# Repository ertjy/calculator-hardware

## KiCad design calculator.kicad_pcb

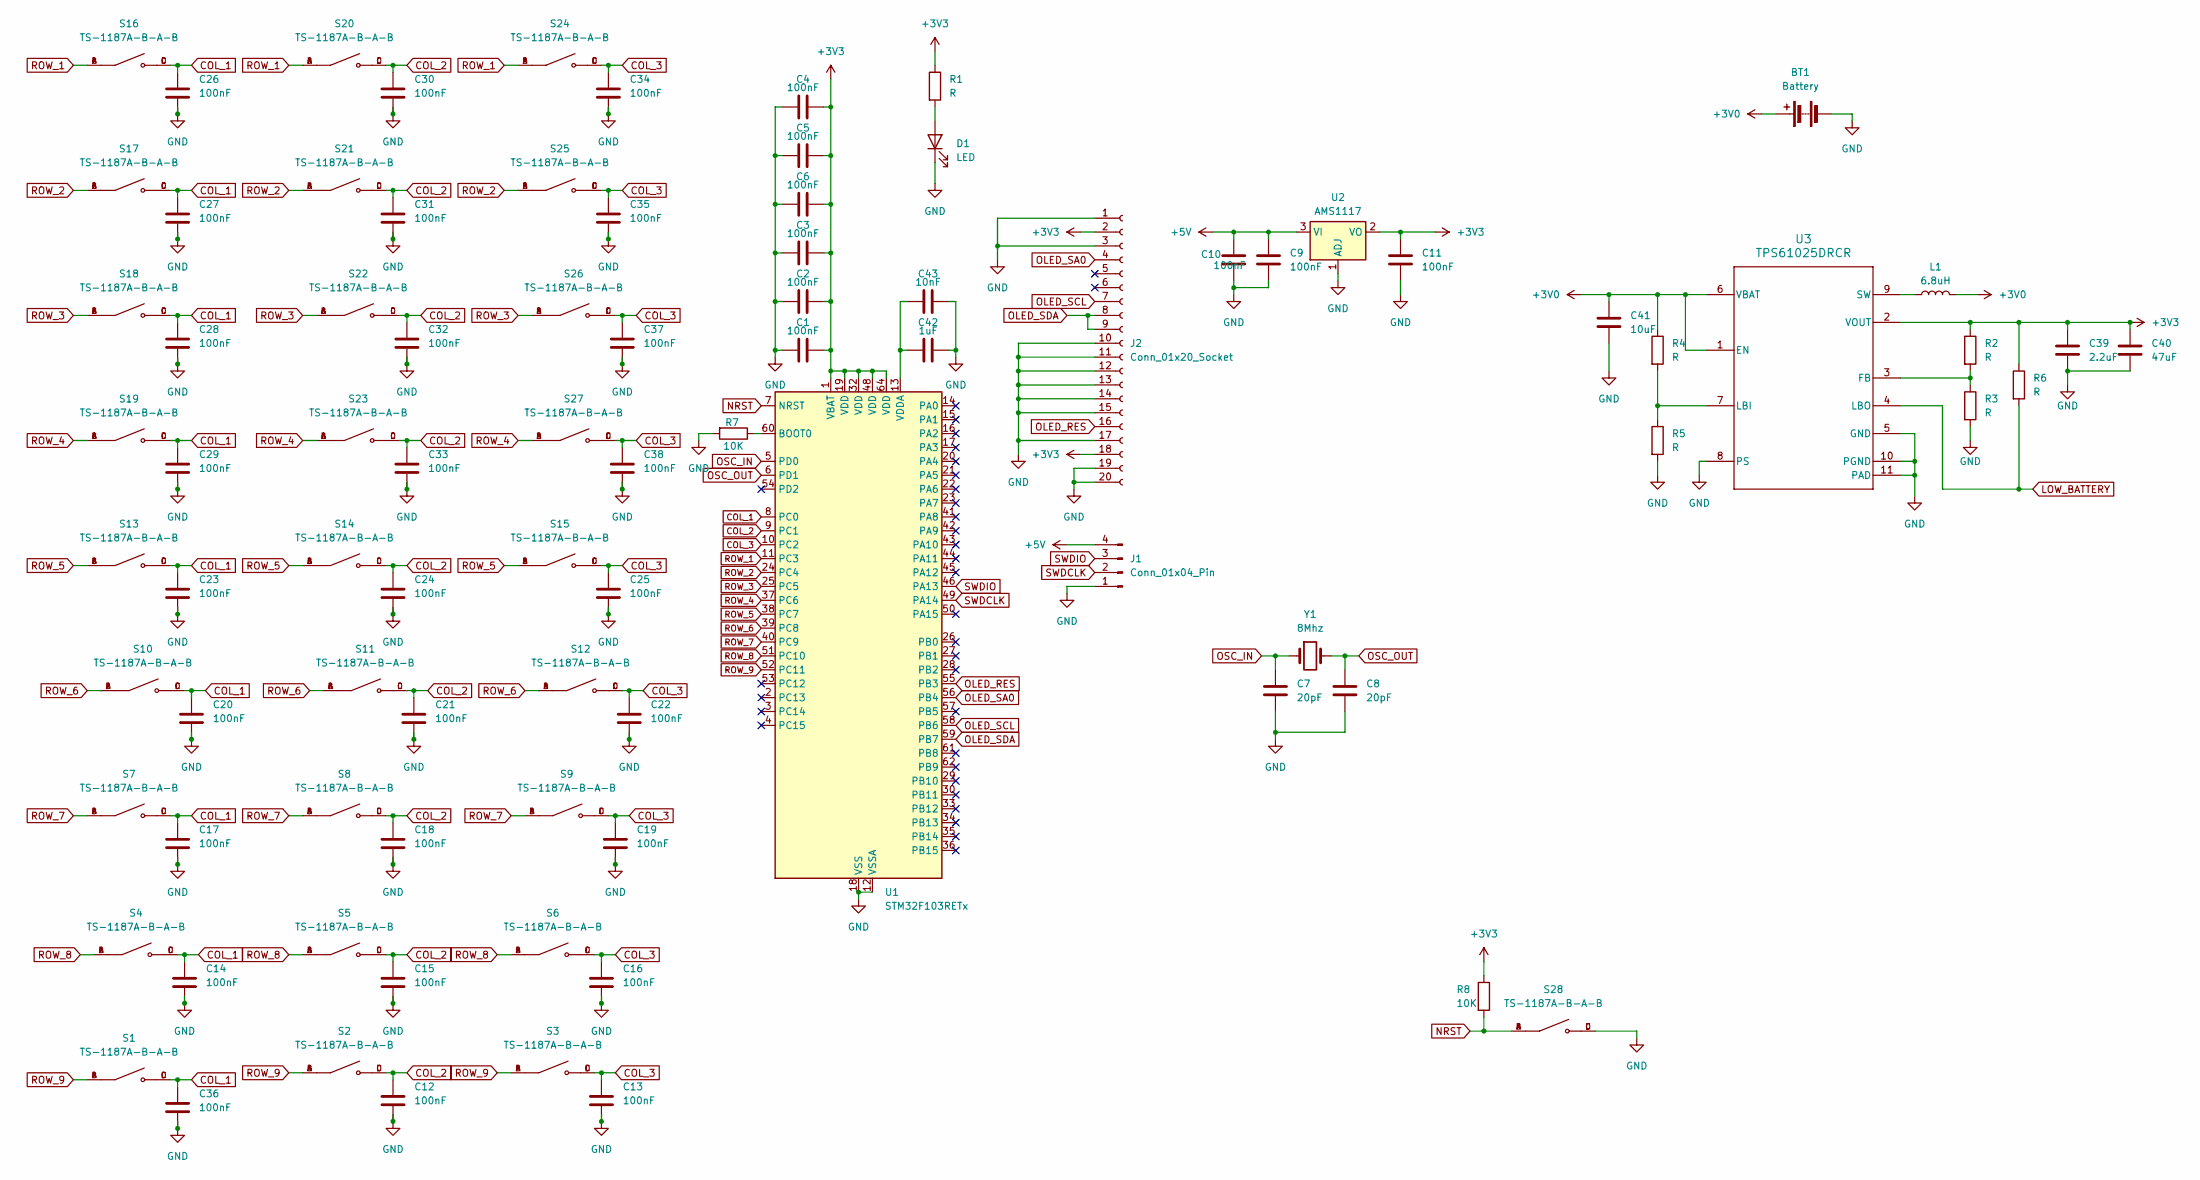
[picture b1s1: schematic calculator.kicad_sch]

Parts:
BT1: Battery; Battery_Pads
C1, C2, C3, C4, C5, C6, C9, C10, C11, C12, C13, C14, C15, C16, C17, C18, C19, C20, C21, C22, C23, C24, C25, C26, C27, C28, C29, C30, C31, C32, C33, C34, C35, C36, C37, C38: 100nF; C_0603_1608Metric
C7, C8: 20pF; C_0603_1608Metric
C39: 2.2uF; C_0603_1608Metric
C40: 47uF; C_0805_2012Metric
C41: 10uF; C_0603_1608Metric
C42: 1uF; C_0603_1608Metric
C43: 10nF; C_0603_1608Metric
D1: LED; LED_0603_1608Metric
J1: Conn_01x04_Pin; PinHeader_1x04_P2.54mm_Vertical
J2: Conn_01x20_Socket; PinSocket_1x20_P2.54mm_Vertical
L1: 6.8uH; IND_NP-4R7NC_SUM
R1, R2, R3, R4, R5, R6: R; R_0201_0603Metric
R7, R8: 10K; R_0201_0603Metric
S1, S2, S3, S4, S5, S6, S7, S8, S9, S10, S11, S12, S13, S14, S15, S16, S17, S18, S19, S20, S21, S22, S23, S24, S25, S26, S27, S28: TS-1187A-B-A-B; SW_TS-1187A-B-A-B; PARTREV A0
U1: STM32F103RETx; LQFP-64_10x10mm_P0.5mm
U2: AMS1117; SOT-223-3_TabPin2
U3: TPS61025DRCR; DRC0010J
Y1: 8Mhz; Crystal_SMD_HC49-SD

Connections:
+3V0: BT1.1 (+), C41.1, L1.2, R4.1, U3.1 (EN), U3.6 (VBAT)
+3V3: C1.2, C2.2, C3.2, C4.2, C5.2, C6.2, C11.1, C39.1, C40.1, J2.2, J2.18, R1.1, R2.1, R6.1, R8.1, U1.1 (VBAT), U1.19 (VDD), U1.32 (VDD), U1.48 (VDD), U1.64 (VDD), U2.2 (VO), U3.2 (VOUT)
+5V: C9.1, C10.2, J1.4, U2.3 (VI)
COL_1: C14.1, C17.1, C20.1, C23.1, C26.1, C27.1, C28.1, C29.1, C36.1, S1.C, S1.D, S4.C, S4.D, S7.C, S7.D, S10.C, S10.D, S13.C, S13.D, S16.C, S16.D, S17.C, S17.D, S18.C, S18.D, S19.C, S19.D, U1.8 (PC0)
COL_2: C12.1, C15.1, C18.1, C21.1, C24.1, C30.1, C31.1, C32.1, C33.1, S2.C, S2.D, S5.C, S5.D, S8.C, S8.D, S11.C, S11.D, S14.C, S14.D, S20.C, S20.D, S21.C, S21.D, S22.C, S22.D, S23.C, S23.D, U1.9 (PC1)
COL_3: C13.1, C16.1, C19.1, C22.1, C25.1, C34.1, C35.1, C37.1, C38.1, S3.C, S3.D, S6.C, S6.D, S9.C, S9.D, S12.C, S12.D, S15.C, S15.D, S24.C, S24.D, S25.C, S25.D, S26.C, S26.D, S27.C, S27.D, U1.10 (PC2)
GND: BT1.2 (-), C1.1, C2.1, C3.1, C4.1, C5.1, C6.1, C7.1, C8.1, C9.2, C10.1, C11.2, C12.2, C13.2, C14.2, C15.2, C16.2, C17.2, C18.2, C19.2, C20.2, C21.2, C22.2, C23.2, C24.2, C25.2, C26.2, C27.2, C28.2, C29.2, C30.2, C31.2, C32.2, C33.2, C34.2, C35.2, C36.2, C37.2, C38.2, C39.2, C40.2, C41.2, C42.2, C43.2, D1.1 (K), J1.1, J2.1, J2.3, J2.10, J2.11, J2.12, J2.13, J2.14, J2.15, J2.17, J2.19, J2.20, R3.2, R5.2, R7.2, S28.C, S28.D, U1.12 (VSSA), U1.18 (VSS), U1.31 (VSS), U1.47 (VSS), U1.63 (VSS), U2.1 (ADJ), U3.5 (GND), U3.8 (PS), U3.10 (PGND), U3.11 (PAD)
LOW_BATTERY: R6.2, U3.4 (LBO)
NRST: R8.2, S28.A, S28.B, U1.7 (NRST)
unnamed: D1.2 (A), R1.2
unnamed: R7.1, U1.60 (BOOT0)
unnamed: C42.1, C43.1, U1.13 (VDDA)
unnamed: R2.2, R3.1, U3.3 (FB)
unnamed: R4.2, R5.1, U3.7 (LBI)
unnamed: L1.1, U3.9 (SW)
OLED_RES: J2.16, U1.55 (PB3)
OLED_SA0: J2.4, U1.56 (PB4)
OLED_SCL: J2.7, U1.58 (PB6)
OLED_SDA: J2.8, J2.9, U1.59 (PB7)
OSC_IN: C7.2, U1.5 (PD0), Y1.1
OSC_OUT: C8.2, U1.6 (PD1), Y1.2
ROW_1: S16.A, S16.B, S20.A, S20.B, S24.A, S24.B, U1.11 (PC3)
ROW_2: S17.A, S17.B, S21.A, S21.B, S25.A, S25.B, U1.24 (PC4)
ROW_3: S18.A, S18.B, S22.A, S22.B, S26.A, S26.B, U1.25 (PC5)
ROW_4: S19.A, S19.B, S23.A, S23.B, S27.A, S27.B, U1.37 (PC6)
ROW_5: S13.A, S13.B, S14.A, S14.B, S15.A, S15.B, U1.38 (PC7)
ROW_6: S10.A, S10.B, S11.A, S11.B, S12.A, S12.B, U1.39 (PC8)
ROW_7: S7.A, S7.B, S8.A, S8.B, S9.A, S9.B, U1.40 (PC9)
ROW_8: S4.A, S4.B, S5.A, S5.B, S6.A, S6.B, U1.51 (PC10)
ROW_9: S1.A, S1.B, S2.A, S2.B, S3.A, S3.B, U1.52 (PC11)
SWDCLK: J1.2, U1.49 (PA14)
SWDIO: J1.3, U1.46 (PA13)

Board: 2 copper layers, 87 parts (0 on the bottom side), 30 nets, no tracks yet.

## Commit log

2024-05-16 Add .gitignore
2024-05-16 Start designing the schematic
2024-05-22 Design more of the pcb
2024-07-07 STACK-46 Implement state reporting
2024-08-14 Finish schematic design
